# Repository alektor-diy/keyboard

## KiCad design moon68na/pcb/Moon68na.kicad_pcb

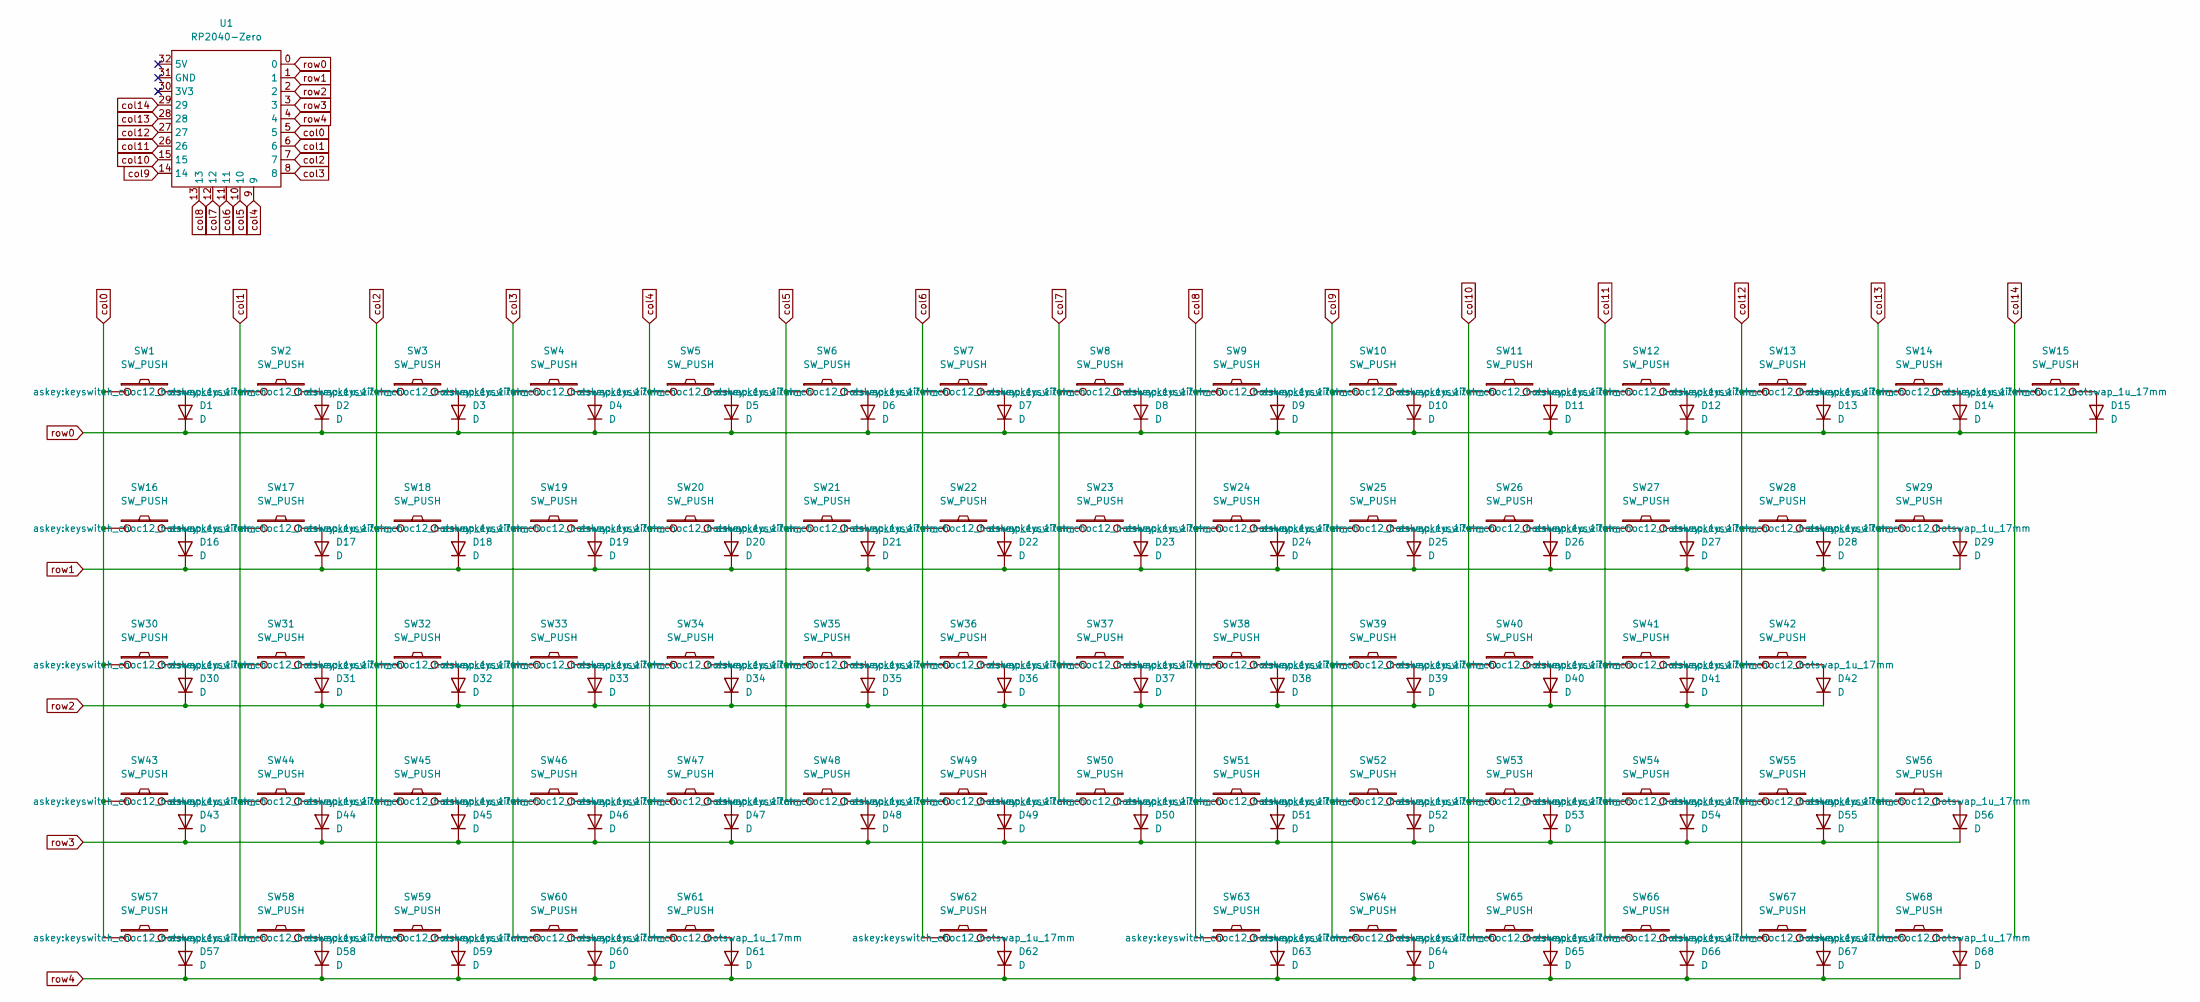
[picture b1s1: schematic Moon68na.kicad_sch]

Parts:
D1, D2, D3, D4, D5, D6, D7, D8, D9, D10, D11, D12, D13, D14, D15, D16, D17, D18, D19, D20, D21, D22, D23, D24, D25, D26, D27, D28, D29, D30, D31, D32, D33, D34, D35, D36, D37, D38, D39, D40, D41, D42, D43, D44, D45, D46, D47, D48, D49, D50, D51, D52, D53, D54, D55, D56, D57, D58, D59, D60, D61, D62, D63, D64, D65, D66, D67, D68: D; Diode_SMD
SW1, SW2, SW3, SW4, SW5, SW6, SW7, SW8, SW9, SW10, SW11, SW12, SW13, SW14, SW15, SW16, SW17, SW18, SW19, SW20, SW21, SW22, SW23, SW24, SW25, SW26, SW27, SW28, SW29, SW30, SW31, SW32, SW33, SW34, SW35, SW36, SW37, SW38, SW39, SW40, SW41, SW42, SW43, SW44, SW45, SW46, SW47, SW48, SW49, SW50, SW51, SW52, SW53, SW54, SW55, SW56, SW57, SW58, SW59, SW60, SW61, SW62, SW63, SW64, SW65, SW66, SW67, SW68: SW_PUSH; keyswitch_choc12_hotswap_1u_17mm
U1: RP2040-Zero; RP2040-Zero-TH

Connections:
unnamed: D1.2 (A), SW1.2
unnamed: D2.2 (A), SW2.2
unnamed: D3.2 (A), SW3.2
unnamed: D4.2 (A), SW4.2
unnamed: D5.2 (A), SW5.2
unnamed: D6.2 (A), SW6.2
unnamed: D7.2 (A), SW7.2
unnamed: D8.2 (A), SW8.2
unnamed: D9.2 (A), SW9.2
unnamed: D10.2 (A), SW10.2
unnamed: D11.2 (A), SW11.2
unnamed: D12.2 (A), SW12.2
unnamed: D13.2 (A), SW13.2
unnamed: D14.2 (A), SW14.2
unnamed: D15.2 (A), SW15.2
unnamed: D16.2 (A), SW16.2
unnamed: D17.2 (A), SW17.2
unnamed: D18.2 (A), SW18.2
unnamed: D19.2 (A), SW19.2
unnamed: D20.2 (A), SW20.2
unnamed: D21.2 (A), SW21.2
unnamed: D22.2 (A), SW22.2
unnamed: D23.2 (A), SW23.2
unnamed: D24.2 (A), SW24.2
unnamed: D25.2 (A), SW25.2
unnamed: D26.2 (A), SW26.2
unnamed: D27.2 (A), SW27.2
unnamed: D28.2 (A), SW28.2
unnamed: D29.2 (A), SW29.2
unnamed: D30.2 (A), SW30.2
unnamed: D31.2 (A), SW31.2
unnamed: D32.2 (A), SW32.2
unnamed: D33.2 (A), SW33.2
unnamed: D34.2 (A), SW34.2
unnamed: D35.2 (A), SW35.2
unnamed: D36.2 (A), SW36.2
unnamed: D37.2 (A), SW37.2
unnamed: D38.2 (A), SW38.2
unnamed: D39.2 (A), SW39.2
unnamed: D40.2 (A), SW40.2
unnamed: D41.2 (A), SW41.2
unnamed: D42.2 (A), SW42.2
unnamed: D43.2 (A), SW43.2
unnamed: D44.2 (A), SW44.2
unnamed: D45.2 (A), SW45.2
unnamed: D46.2 (A), SW46.2
unnamed: D47.2 (A), SW47.2
unnamed: D48.2 (A), SW48.2
unnamed: D49.2 (A), SW49.2
unnamed: D50.2 (A), SW50.2
unnamed: D51.2 (A), SW51.2
unnamed: D52.2 (A), SW52.2
unnamed: D53.2 (A), SW53.2
unnamed: D54.2 (A), SW54.2
unnamed: D55.2 (A), SW55.2
unnamed: D56.2 (A), SW56.2
unnamed: D57.2 (A), SW57.2
unnamed: D58.2 (A), SW58.2
unnamed: D59.2 (A), SW59.2
unnamed: D60.2 (A), SW60.2
unnamed: D61.2 (A), SW61.2
unnamed: D62.2 (A), SW62.2
unnamed: D63.2 (A), SW63.2
unnamed: D64.2 (A), SW64.2
unnamed: D65.2 (A), SW65.2
unnamed: D66.2 (A), SW66.2
unnamed: D67.2 (A), SW67.2
unnamed: D68.2 (A), SW68.2
col0: SW1.1, SW16.1, SW30.1, SW43.1, SW57.1, U1.5
col1: SW2.1, SW17.1, SW31.1, SW44.1, SW58.1, U1.6
col2: SW3.1, SW18.1, SW32.1, SW45.1, SW59.1, U1.7
col3: SW4.1, SW19.1, SW33.1, SW46.1, SW60.1, U1.8
col4: SW5.1, SW20.1, SW34.1, SW47.1, SW61.1, U1.9
col5: SW6.1, SW21.1, SW35.1, SW48.1, U1.10
col6: SW7.1, SW22.1, SW36.1, SW49.1, SW62.1, U1.11
col7: SW8.1, SW23.1, SW37.1, SW50.1, U1.12
col8: SW9.1, SW24.1, SW38.1, SW51.1, SW63.1, U1.13
col9: SW10.1, SW25.1, SW39.1, SW52.1, SW64.1, U1.14
col10: SW11.1, SW26.1, SW40.1, SW53.1, SW65.1, U1.15
col11: SW12.1, SW27.1, SW41.1, SW54.1, SW66.1, U1.26
col12: SW13.1, SW28.1, SW42.1, SW55.1, SW67.1, U1.27
col13: SW14.1, SW29.1, SW56.1, SW68.1, U1.28
col14: SW15.1, U1.29
row0: D1.1 (K), D2.1 (K), D3.1 (K), D4.1 (K), D5.1 (K), D6.1 (K), D7.1 (K), D8.1 (K), D9.1 (K), D10.1 (K), D11.1 (K), D12.1 (K), D13.1 (K), D14.1 (K), D15.1 (K), U1.0
row1: D16.1 (K), D17.1 (K), D18.1 (K), D19.1 (K), D20.1 (K), D21.1 (K), D22.1 (K), D23.1 (K), D24.1 (K), D25.1 (K), D26.1 (K), D27.1 (K), D28.1 (K), D29.1 (K), U1.1
row2: D30.1 (K), D31.1 (K), D32.1 (K), D33.1 (K), D34.1 (K), D35.1 (K), D36.1 (K), D37.1 (K), D38.1 (K), D39.1 (K), D40.1 (K), D41.1 (K), D42.1 (K), U1.2
row3: D43.1 (K), D44.1 (K), D45.1 (K), D46.1 (K), D47.1 (K), D48.1 (K), D49.1 (K), D50.1 (K), D51.1 (K), D52.1 (K), D53.1 (K), D54.1 (K), D55.1 (K), D56.1 (K), U1.3
row4: D57.1 (K), D58.1 (K), D59.1 (K), D60.1 (K), D61.1 (K), D62.1 (K), D63.1 (K), D64.1 (K), D65.1 (K), D66.1 (K), D67.1 (K), D68.1 (K), U1.4

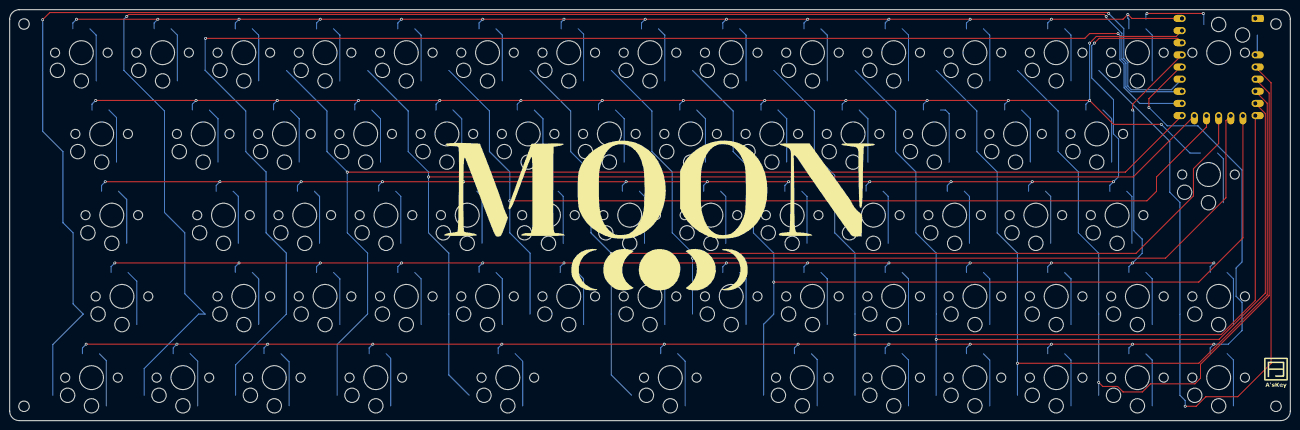
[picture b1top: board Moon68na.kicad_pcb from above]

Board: 2 copper layers, 268.0 x 86.0 mm, 141 parts (0 on the bottom side), 88 nets.

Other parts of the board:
Ref**: Val**; m2_Screw_Hole
Ref**#2, Ref**#3, Ref**#4: Val**; m2_Screw_Hole

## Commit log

2024-08-05 rename via.json
2024-08-05 Create JP81Fビルドガイド
2024-08-05 Rename JP81Fビルドガイド to JP81Fビルドガイド.md
2024-08-07 Rename JP81Fビルドガイド.md to JP81F_buildguide.md
2024-08-30 upload fw files.
    earth95s
    earth87lcd
2024-08-30 upload product photos.
2024-09-01 Upload PCB files.
2024-09-02 upload PCB data.
2024-09-18 upload files of earth72alice.
2024-10-31 create files for hawk44.
2024-11-06 create files of insight10.
2024-11-12 upload temp files.
2024-12-02 create moon83s files.
2025-02-20 create files of mars74g.
2025-03-18 upload earth87sw files.
2025-04-18 upload
2026-02-20 fiix
2026-06-21 updata
